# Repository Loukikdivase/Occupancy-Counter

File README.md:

# Occupancy Counter

by: Loukik-Sachin Divase, Rudy Marvyn Kalisetty-Appadu

**Faculty of Technology and Bionics**

***Rhine-Waal University of Applied Sciences***

Date: 16 January 2025

----

## Abstract

The occupancy counter is designed to ensure a seamless flow of people, especially on a busy day. The system tracks the number of people entering and exiting a room and can be used for libraries, offices, toilets, labs, and more. It features real-time monitoring, status indication using LEDs, compliance with safety regulations, and energy-efficient operation. A microcontroller with IR sensors detects directional movement, updates the LCD display accordingly.

## Table of Contents

- [Abstract](#abstract)
- [1 Introduction](#1-introduction)
- [2 Theory](#2-theory)
- [3 Methodology](#3-methodology)
  - [3.1 Hardware](#31-hardware)
  - [3.2 Software](#32-software)
- [4 Bill of Materials (BOM)](#4-bill-of-materials-bom)
- [5 Results](#5-results)
  - [5 Prototype](#50-prototype)
  - [5.1 Schematic](#51-schematic)
  - [5.2 Board](#52-board)
  - [5.3 UV Masking](#53-uv-masking)
  - [5.4 Etching](#54-etching)
  - [5.5 Drilling](#55-drilling)
  - [5.6 Baking](#56-baking)
  - [5.7 Testing](#57-testing)
  - [5.8 Outsourcing](#58-outsourcing)
- [6 Discussion](#6-discussion)
- [7 Conclusion](#7-conclusion)
- [8 Power Consumption](#8-power-consumption)
- [9 References](#9-references)

## 1 Introduction

Managing space efficiently in crowded environments can be challenging. The people counter helps address this issue by providing real-time tracking of room occupancy.

## 2	Theory

The occupancy counter relies on IR sensors to detect movement direction. The system uses logic to determine whether a person enters or exits, ensuring accurate count tracking. If a person passes through sensor 1(placed outside the room near the door) and sensor 2(placed inside the room near the door), the sensor will count. The sensor will increase the count by 1 if a person passes sensor 1 before sensor 2. The sensor will decrease the count by 1 if the person passes sensor 2 before sensor 1.

## 3	Methodology

### 3.1 Hardware

The system consists of:  
•	Microcontroller (ATmega328p)   
•	16MHz Crystal Oscillator  
•	Infrared LED and photodiode  
•	LCD display (16x2)  
•	Buzzer    
•	LED indicators (Red/Green/Yellow)   
•	battery  
•	Voltage regulator (LM7805)   
•	Dual Comparator (LM393)  
•	resistors  
•	capacitors  
•	inductor  
•	switches  

### 3.2 Software

•	Notepad++ for writing the main program  
•	myAVRboard MK2 for flashing the ATmega328p microcontroller  
•	The program tracks occupancy using IR sensor logic and updates the display accordingly.  

#### Code Snippets

//Reset lock for sensor 1 when signal goes HIGH  

if (sensor1_state && sensor1_locked)  
{  
     sensor1_locked = 0; //Reset lock  
}
            
//Reset lock for sensor 2 when signal goes HIGH  

if (sensor2_state && sensor2_locked)  
{  
     sensor2_locked = 0;  // Reset lock  
}  

## 4 BOM

| No. | Qty. | Manufacturer | Component | Ordering Code (Manufacturer) | Vendor | Ordering Code (Vendor) | Price per Unit (€) | Price (€) | Link |
|----|----|--------------|-----------|-------------------------|--------|----------------|----------------|----------|------|
| 1  | 1  | Texas Instruments | 5V Voltage Regulator SMD | LM7805MPX/NOPB | Mouser | 595-LM7805MPX/NOPB | 1.31 | 1.31 | [Link](https://www.mouser.de/ProductDetail/Texas-Instruments/LM7805MPX-NOPB?qs=gO6GG99qvRCSwIVAoVKHPw%3D%3D) |
| 2  | 4  | Atmel | ATmega328P-PU S | - | HSRW | 1712 | 2.51 | 2.51 |  |
| 3  | 4  | - | 16MHz Crystal Oscillator | QD LFXTALO03240 | Reichelt | - | 0.43 | 0.43 | [Link](https://www.reichelt.de/standardquarz-grundton-16-mhz-iqd-lfxtal003240-p245409.html?&trstct=pos_0&nbc=1) |
| 4  | 2  | - | 22pF Capacitor | RND 150MT15N2202 | Reichelt | - | 0.02 | 0.04 | [Link](https://www.reichelt.de/smd-kerko-0402-22-pf-16-v-1-mlec-rnd-150mt15n2202-p225449.html?&trstct=pos_4&nbe=1) |
| 5  | 4  | - | 10k Ohm Resistor | - | HSRW | 621 | 0.01 | 0.04 | [Link](https://ee.hsrw.org/) |
| 6  | 2  | Vishay/BC Components | 220uF Capacitor, 10V DC | MAL214097403E3 | Mouser | 594-MAL214097403E3 | 1.97 | 3.94 | [Link](https://www.mouser.de/ProductDetail/Vishay-BC-Components/MAL214097403E3?qs=aJI9t0tCUIVP9cSclwINCQ%3D%3D) |
| 7  | 5  | - | LEDs | - | HSRW | 471,497,498 | 0.06 | 0.24 | [Link](https://ee.hsrw.org/) |
| 8  | 7  | - | 220 Ohm Resistor | - | HSRW | 579 | 0.01 | 0.07 | [Link](https://ee.hsrw.org/) |
| 9  | 1  | - | LCD Display 16x2 | DEBO LCD16X2 BL | Reichelt | - | 4.65 | 4.65 | [Link](https://www.reichelt.de/entwicklerboards-display-16-x-2-zeichen-blau-debo-led16x2-bl-p335002.html?&trstct=pos_1&nbe=1) |
| 10 | 1  | - | 28-Pin IC Socket | - | HSRW | 630 | 0.21 | 0.21 | [Link](https://ee.hsrw.org/) |
| 11 | 2  | - | Push Button | TASTER 9305 | Reichelt | - | 0.20 | 0.40 | [Link](https://www.reichelt.de/kurzhubtaster-6x6mm-hoehe-8-Omm-12v-vertikal-taster-9305-p44586.html) |
| 12 | 2  | Everlight | Infrared Diode (940nm, emitter) | IR 7373C EVL | Reichelt | - | 0.15 | 0.30 | [Link](https://www.reichelt.de/infrarot-diode-gaalas-940-nm-50-5-mm-t-1-3-4-ir-7373c-evl-p219706.html?&trstct=vrt_pdn&nbe=1) |
| 13 | 6  | - | 0.1µF Capacitor SM | 0.1/63RAD | HSRW | 372 | 0.03 | 0.18 | [Link](https://ee.hsrw.org/) |
| 14 | 2  | Vishay | Phototransistor (Receiver) | BPV10NF | Reichelt | - | 0.35 | 0.70 | [Link](https://www.reichelt.de/pin-fotodiode-5mm-tageslichfilter-20-60-a-870-950nm-bpv-10nf-p146650.html?&trstct=vrt_pdn&nbe=1) |
| 15 | 4  | Aragonesa de Components | Potentiometer (10k Ohm) | ACP 6-S 10K | Reichelt | - | 0.21 | 0.84 | [Link](https://www.reichelt.de/einstellpotentiometer-stehend-10-kohm-6-mm-acp-6-s-10k-p110242.html?&trstct=vrt_pdn&nbe=1) |
| 16 | 1  | STMicroelectronics | LM393 Comparator | LM393 D STM | Reichelt | - | 0.21 | 0.21 | [Link](https://www.reichelt.de/komparator-18v-36v-2-fach-so-8-lm-393-d-stm-p348702.html?&trstct=pos_O&nbe=1) |
| 17 | 1  | - | 2-Pin Angled Connector (Male) | PSS 254/3W | Reichelt | - | 0.06 | 0.06 | [Link](https://www.reichelt.de/printstecker-einzelstecker-gewinkelt-3-polig-pss-254-3w-p14910.html) |
| 18 | 1  | OURNS | 10µH Inductor, 10% Tolerance | CC453232A-100KL | Mouser | 652-CC453232A-100KL | 0.47 | 0.47 | [Link](https://www.mouser.de/ProductDetail/Bourns/CC453232A-100KL?qs=sPbYRqrBIVk4tmhOTVDWBA%3D%3D) |
| 19 | 1  | - | Battery | - | HSRW | - | 1.00 | 1.00 | [Link](https://ee.hsrw.org/) |
| 20 | 1  | - | 3-Pin Switch | - | HSRW | - | 1.35 | 1.35 | [Link](https://ee.hsrw.org/) |
| 21 | 1  | - | Male Headers | - | HSRW | - | 1.00 | 1.00 | [Link](https://ee.hsrw.org/) |
| 22 | 1  | - | Buzzer | - | HSRW | - | 0.50 | 0.50 | [Link](https://ee.hsrw.org/) |
| 23 | 1  | - | NPN Transistor BC547 | - | HSRW | - | 0.36 | 0.36 | [Link](https://ee.hsrw.org/) |

## 5	Results

### Prototype

### 5.1 Schematic

### 5.2 board

### 5.3 UV Masking

### 5.4 Etching

### 5.5 Drilling

### 5.6 Baking

### 5.7 Testing

### 5.8 Outsourcing

## version 2 (additional)

### Schematic

### Board

## 6	Discussion

The system performs well in controlled conditions. However, environmental factors such as lighting variations may affect sensor accuracy. Calibration is necessary for optimal performance.

What exactly happens? 
The person must pass both sensors to register the count since our product is directional.

## 7	Conclusion

As aspiring engineers, we believe that this project was a success. However, there might be some unsolved challenges that we did not encounter, and we would be more than happy to address them in the future. Future work could involve integrating wireless data transmission for monitoring remotely.

## 8	Power Consumption

Total power consumption: 1.29W, where V = 6V and I = 0.22A

Actual useful power consumption: 1W,  where V = 4.85V and I = 0.21A.

## 9	References

* [1] https://shop.myavr.de/Systemboards%20und%20Programmer/myAVR%20Board%20MK2,%20best%C3%BCckt.htm?sp=article.sp.php&artID=40

* [2] https://docs.arduino.cc/hardware/uno-rev3/

* [3] https://github.com/Loukikdivase/Occupancy-Counter/tree/main/resources

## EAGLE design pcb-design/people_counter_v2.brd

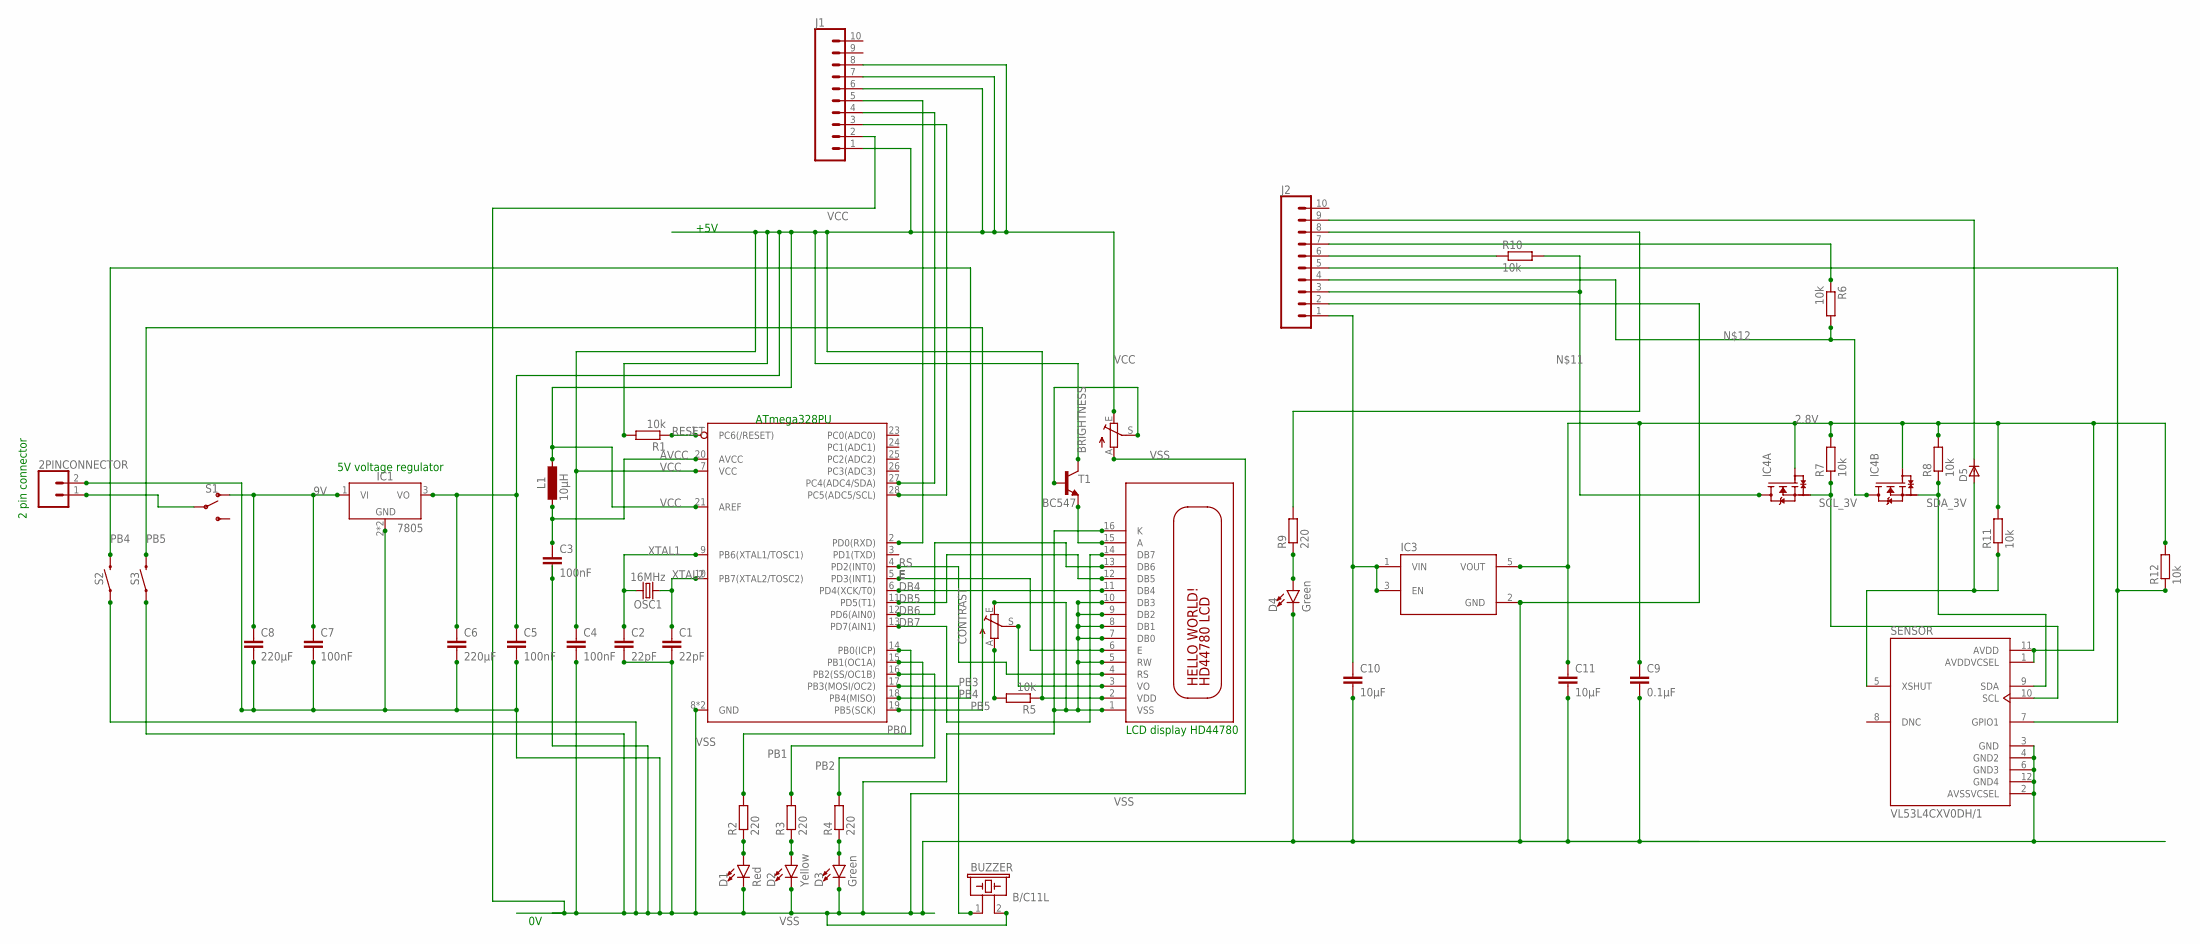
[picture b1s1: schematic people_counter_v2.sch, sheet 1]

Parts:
2PINCONNECTOR: CONN_02; 1X02
BRIGHTNESS: TRIM_EU-PT10S; PT-10S
BUZZER: B/C11L
C1, C2: 22pF; C0805
C3, C4, C5, C7: 100nF; C0805
C6, C8: 220µF; C0805
C9: 0.1µF; C0805
C10, C11: 10µF; C0805
CONTRAST: TRIM_EU-PT10S; PT-10S
D1: Red; LED-0603
D2: Yellow; LED-0603
D3, D4: Green; LED-0603
D5: 1N4148WS; SOD323F
IC1: 7805; SOT230P700X170-4
IC2: 328P; DIP28
IC3: MIC5504-2.8YM5-TR; SOT95P280X145-5N
IC4: DMN63D8LDW-7; SOT363
J1, J2: CONN_10"; 1X10
L1: 10µH; L1812
OSC1: 16MHz; HC49US
R1, R5, R6, R7, R8, R10, R11, R12: 10k; R0603
R2, R3, R4, R9: 220; R0603
S1: SWITCH-SPDT-PTH-11.6X4.0MM; SWITCH_SPDT_PTH_11.6X4.0MM
S2, S3: MOMENTARY-SWITCH-SPST-PTH-6.0MM; TACTILE_SWITCH_PTH_6.0MM
SENSOR: VL53L4CXV0DH/1; XCDR_VL53L4CXV0DH/1
T1: BC547; TO92
X1: HD44780LCD-1602; LCD1602

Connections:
2.8V: C9.1, C11.1, IC3.5 (VOUT), IC4.G1 (G), IC4.G2 (G), R7.2, R8.2, R11.2, R12.2, SENSOR.1 (AVDDVCSEL), SENSOR.11 (AVDD)
9V: C7.1, C8.1, IC1.1 (VI), S1.1 (O)
AVCC: C3.1, IC2.20 (AVCC), L1.2
DB4: IC2.6 (PD4(XCK/T0)), X1.11 (DB4)
DB5: IC2.11 (PD5(T1)), X1.12 (DB5)
DB6: IC2.12 (PD6(AIN0)), X1.13 (DB6)
DB7: IC2.13 (PD7(AIN1)), X1.14 (DB7)
E: IC2.5 (PD3(INT1)), X1.6 (E)
GREEN: D3.A, R4.1
unnamed: J2.6, R10.1
unnamed: D4.A, R9.1
unnamed: D5.C, J2.9
unnamed: 2PINCONNECTOR.1, S1.2
unnamed: IC2.2 (PD0(RXD)), J1.5
unnamed: D5.A, R11.1, SENSOR.5 (XSHUT)
unnamed: CONTRAST.A, R5.2
unnamed: J2.5, R12.1, SENSOR.7 (GPIO1)
unnamed: IC4.D1 (D), J2.3, R10.2
unnamed: IC4.D2 (D), J2.4, R6.2
unnamed: BRIGHTNESS.S, T1.2 (B)
unnamed: J2.8, R9.2
unnamed: J2.7, R6.1
unnamed: C10.1, IC3.1 (VIN), IC3.3 (EN), J2.1
unnamed: T1.1 (E), X1.15 (A)
PB0: IC2.14 (PB0(ICP)), R2.2
PB1: IC2.15 (PB1(OC1A)), R3.2
PB2: IC2.16 (PB2(SS/OC1B)), R4.2
PB3: BUZZER.1, IC2.17 (PB3(MOSI/OC2))
PB4: IC2.18 (PB4(MISO)), S2.3 (2)
PB5: IC2.19 (PB5(SCK)), S3.3 (2)
RED: D1.A, R2.1
RESET: IC2.1 (PC6(/RESET)), R1.1
RS: IC2.4 (PD2(INT0)), X1.4 (RS)
SCL_3V: IC4.S1 (S), R7.1, SENSOR.10 (SCL)
SCL_5V: IC2.28 (PC5(ADC5/SCL)), J1.3
SDA_3V: IC4.S2 (S), R8.1, SENSOR.9 (SDA)
SDA_5V: IC2.27 (PC4(ADC4/SDA)), J1.4
VCC: BRIGHTNESS.E, C4.1, C5.1, C6.1, IC1.3 (VO), IC2.7 (VCC), IC2.21 (AREF), J1.1, J1.6, J1.7, J1.8, L1.1, R1.2, R5.1, T1.3 (C), X1.2 (VDD)
VO: CONTRAST.S, X1.3 (VO)
VSS: 2PINCONNECTOR.2, BRIGHTNESS.A, BUZZER.2, C1.2, C2.2, C3.2, C4.2, C5.2, C6.2, C7.2, C8.2, C9.2, C10.2, C11.2, CONTRAST.E, D1.C, D2.C, D3.C, D4.C, IC1.2 (GND), IC1.4 (GND), IC2.8 (GND), IC2.22 (GND), IC3.2 (GND), J1.2, J2.2, S2.1, S3.1, SENSOR.2 (AVSSVCSEL), SENSOR.3 (GND), SENSOR.4 (GND2), SENSOR.6 (GND3), SENSOR.12 (GND4), X1.1 (VSS), X1.5 (RW), X1.7 (DB0), X1.8 (DB1), X1.9 (DB2), X1.10 (DB3), X1.16 (K)
XTAL1: C2.1, IC2.9 (PB6(XTAL1/TOSC1)), OSC1.2
XTAL2: C1.1, IC2.10 (PB7(XTAL2/TOSC2)), OSC1.1
YELLOW: D2.A, R3.1

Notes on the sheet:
5V voltage regulator
2 pin connector
+5V
ATmega328PU
LCD display HD44780

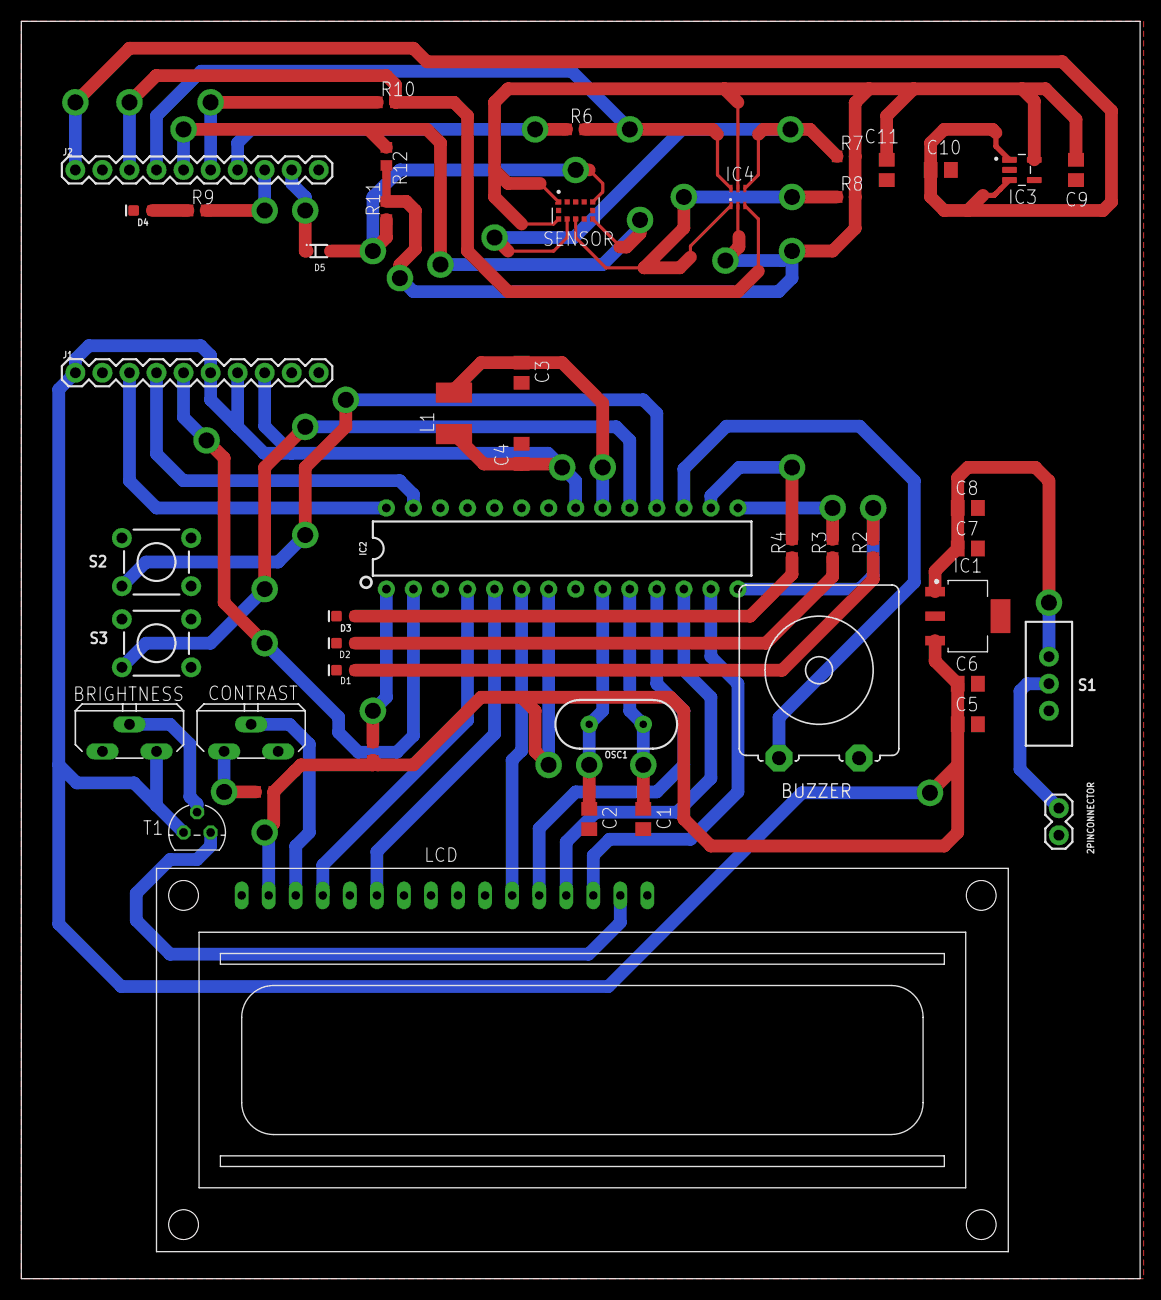
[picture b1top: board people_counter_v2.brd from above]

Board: 2 copper layers, 105.1 x 118.1 mm, 46 parts (0 on the bottom side), 43 nets.

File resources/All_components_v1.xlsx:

Components | Values for resistors (R1 - R11), potentiometers (P1 - P4) in Ohms , capacitors 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 | Remarks | Status
R1 | 10k | Ordered | In use
R2 | 220 | Ordered | In use
R3 | 220 | Ordered | In use
R4 | 220 | Ordered | In use
R5 | 10k | Ordered | In use
R6 | 220 | Ordered | In use
R7 | 220 | Ordered | In use
R8 | 220 | Ordered | In use
R9 | 220 | Ordered | In use
R10 | 10k | Ordered | In use
R11 | 10k | Ordered | In use
C1 | 22p | Ordered | In use
C2 | 22p | Ordered | In use
C3 | 100n | Ordered | In use
C4 | 100n | Ordered | In use
C5 | 100n | Ordered | In use
C6 | 220u | Ordered | In use
C7 | 100n | Ordered | In use
C8 | 220u | Ordered | In use
C9 | 0.1u | Ordered | In use
C10 | 0.1u | Ordered | In use
D1 (IN4001) |  | Ordered | In use
D1 | Red | Ordered | In use
D2 | Yellow | Ordered | In use
D3 | Green | Ordered | In use
D4 | IR (infra red - emitter) - transparent | Ordered | In use
D5 | PT (Photo transistor - receiver) - black | Ordered | In use
D6 | IR (infra red - emitter) - transparent | Ordered | In use
D7 | PT (Photo transistor - receiver) - black | Ordered | In use
D8 | Blue | Ordered | In use
D9 | Blue | Ordered | In use
IC1 | 5V voltage regulator (TS 7805) | Ordered | In use
IC2 | Atmega328P | Ordered | In use
IC3 | LM393 | Ordered | In use
L1 | 10u | Ordered | In use
T1 | NPN transistor | Ordered | In use
S1 | 3 pins switch | Ordered | In use
LCD 16 x 2 (HD44780) |  | Ordered | In use
Potentiometer (for contrast on the LCD screen) | 10k | Ordered | In use
Potentiometer (for brightness on the LCD screen) | 10k | Ordered | In use
Potentiometer (for sensitivity for the IR sensor 1) | 10k | Ordered | In use
Potentiometer (for sensitivity for the IR sensor 2) | 10k | Ordered | In use
Crystal oscillator (Osc1) | 16M | Ordered | In use
2 pins straight connector (for battery) |  | Ordered | In use
Push buttons 1 |  | Ordered | In use
Push buttons 2 |  | Ordered | In use
28-Pin socket for the chip |  | Ordered | In use
USB 2.0 type B mini socket (female) |  | Ordered | not in use
Buzzer |  | Ordered | In use

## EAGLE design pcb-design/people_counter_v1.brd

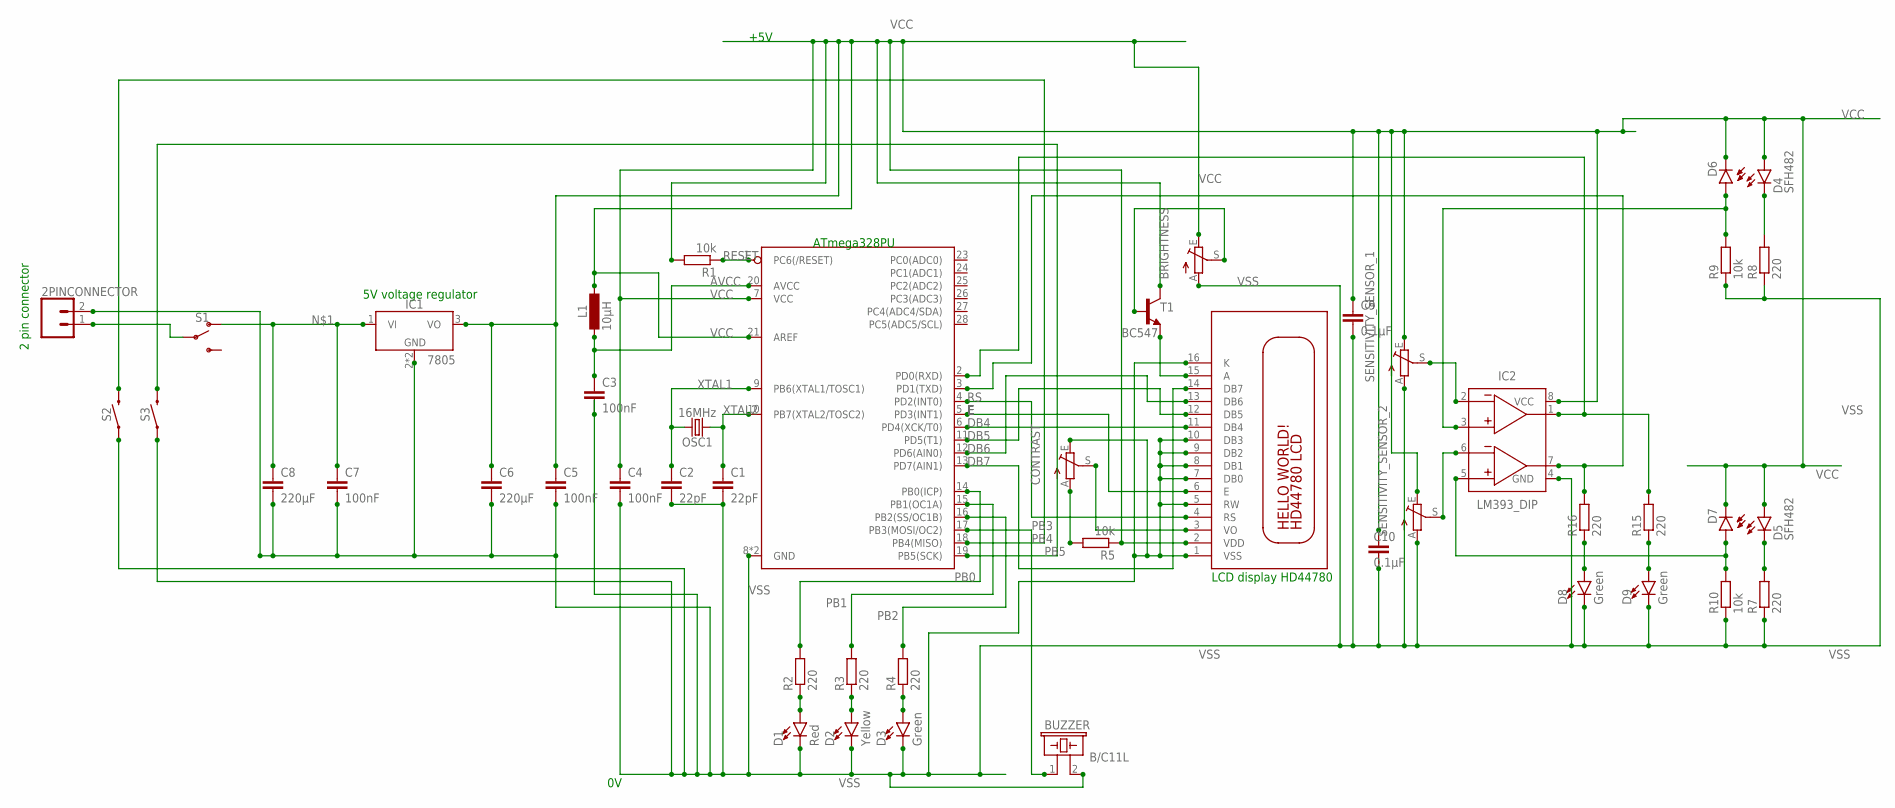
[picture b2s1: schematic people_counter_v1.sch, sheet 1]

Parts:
2PINCONNECTOR: CONN_02; 1X02
BRIGHTNESS: TRIM_EU-PT10S; PT-10S
BUZZER: B/C11L
C1, C2: 22pF; C0805
C3, C4, C5, C7: 100nF; C0805
C6, C8: 220µF; C0805
C9, C10: 0.1µF; C0805
CONTRAST: TRIM_EU-PT10S; PT-10S
D1: Red; LED-0603
D2: Yellow; LED-0603
D3, D8, D9: Green; LED-0603
D4, D5: SFH482
D6, D7: BP104
IC1: 7805; SOT230P700X170-4
IC2: LM393_DIP; DIP826W53P254L959H508Q8B
L1: 10µH; L1812
OSC1: 16MHz; HC49US
R1, R5, R9, R10: 10k; R0603
R2, R3, R4, R7, R8, R15, R16: 220; R0603
S1: SWITCH-SPDT-PTH-11.6X4.0MM; SWITCH_SPDT_PTH_11.6X4.0MM
S2, S3: MOMENTARY-SWITCH-SPST-PTH-6.0MM; TACTILE_SWITCH_PTH_6.0MM
SENSITIVITY_SENSOR_1, SENSITIVITY_SENSOR_2: TRIM_EU-PT10S; PT-10S
T1: BC547; TO92
U1: 328P; DIP28
X1: HD44780LCD-1602; LCD1602

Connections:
AVCC: C3.1, L1.2, U1.20 (AVCC)
DB4: U1.6 (PD4(XCK/T0)), X1.11 (DB4)
DB5: U1.11 (PD5(T1)), X1.12 (DB5)
DB6: U1.12 (PD6(AIN0)), X1.13 (DB6)
DB7: U1.13 (PD7(AIN1)), X1.14 (DB7)
E: U1.5 (PD3(INT1)), X1.6 (E)
unnamed: C7.1, C8.1, IC1.1 (VI), S1.1 (O)
unnamed: BRIGHTNESS.S, T1.2 (B)
unnamed: 2PINCONNECTOR.1, S1.2
unnamed: D1.A, R2.1
unnamed: D2.A, R3.1
unnamed: CONTRAST.A, R5.2
unnamed: D3.A, R4.1
unnamed: D6.A, IC2.3 (+IN1), R9.2
unnamed: D7.A, IC2.5 (+IN2), R10.2
unnamed: D5.K (C), R7.2
unnamed: D4.K (C), R8.2
unnamed: IC2.1 (OUT1), R15.2, U1.2 (PD0(RXD))
unnamed: IC2.7 (OUT2), R16.2, U1.3 (PD1(TXD))
unnamed: IC2.2 (-IN1), SENSITIVITY_SENSOR_1.S
unnamed: IC2.6 (-IN2), SENSITIVITY_SENSOR_2.S
unnamed: T1.1 (E), X1.15 (A)
unnamed: D9.A, R15.1
unnamed: D8.A, R16.1
PB0: R2.2, U1.14 (PB0(ICP))
PB1: R3.2, U1.15 (PB1(OC1A))
PB2: R4.2, U1.16 (PB2(SS/OC1B))
PB3: BUZZER.1, U1.17 (PB3(MOSI/OC2))
PB4: S2.3 (2), U1.18 (PB4(MISO))
PB5: S3.3 (2), U1.19 (PB5(SCK))
RESET: R1.1, U1.1 (PC6(/RESET))
RS: U1.4 (PD2(INT0)), X1.4 (RS)
VCC: BRIGHTNESS.E, C4.1, C5.1, C6.1, C9.1, C10.1, D4.A, D5.A, D6.K (C), D7.K (C), IC1.3 (VO), IC2.8 (VCC), L1.1, R1.2, R5.1, SENSITIVITY_SENSOR_1.E, SENSITIVITY_SENSOR_2.E, T1.3 (C), U1.7 (VCC), U1.21 (AREF), X1.2 (VDD)
VO: CONTRAST.S, X1.3 (VO)
VSS: 2PINCONNECTOR.2, BRIGHTNESS.A, BUZZER.2, C1.2, C2.2, C3.2, C4.2, C5.2, C6.2, C7.2, C8.2, C9.2, C10.2, CONTRAST.E, D1.C, D2.C, D3.C, D8.C, D9.C, IC1.2 (GND), IC1.4 (GND), IC2.4 (GND), R7.1, R8.1, R9.1, R10.1, S2.1, S3.1, SENSITIVITY_SENSOR_1.A, SENSITIVITY_SENSOR_2.A, U1.8 (GND), U1.22 (GND), X1.1 (VSS), X1.5 (RW), X1.7 (DB0), X1.8 (DB1), X1.9 (DB2), X1.10 (DB3), X1.16 (K)
XTAL1: C2.1, OSC1.2, U1.9 (PB6(XTAL1/TOSC1))
XTAL2: C1.1, OSC1.1, U1.10 (PB7(XTAL2/TOSC2))

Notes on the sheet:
5V voltage regulator
2 pin connector
+5V
ATmega328PU
LCD display HD44780

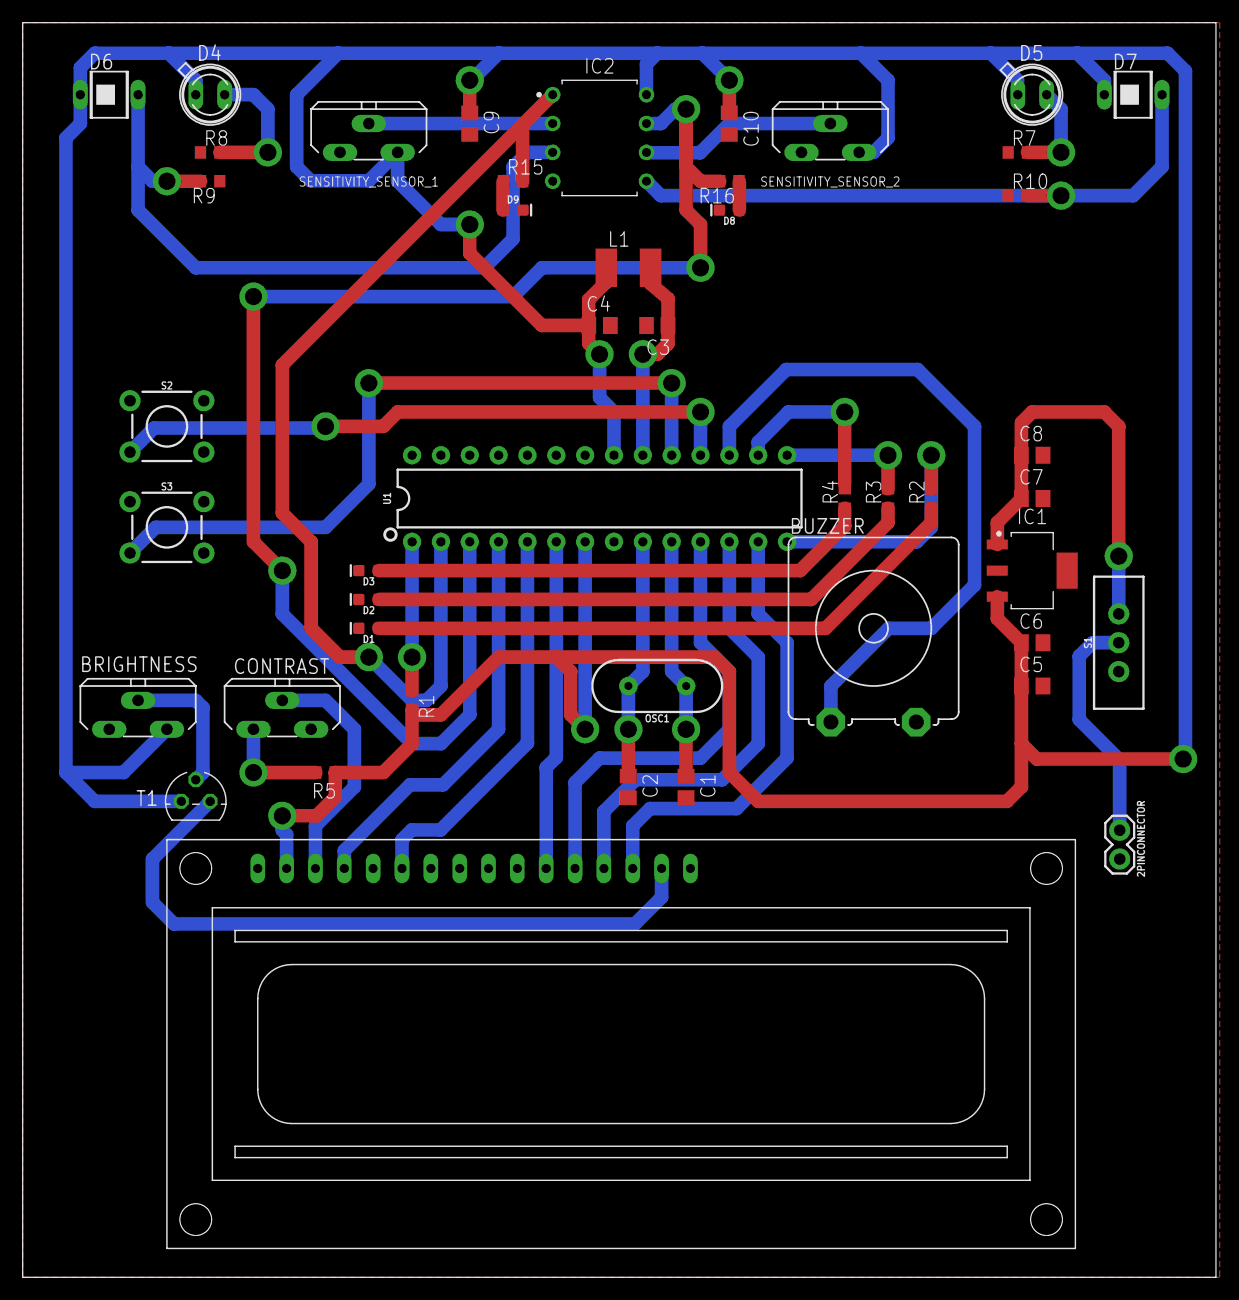
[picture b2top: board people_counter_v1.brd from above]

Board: 2 copper layers, 105.1 x 110.5 mm, 46 parts (0 on the bottom side), 37 nets.

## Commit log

2025-01-16 Create project-idea
2025-01-16 Create presentation
2025-01-16 Create hhh

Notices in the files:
parts and their libraries:
SparkFun-Connectors: Licensing: Creative Commons ShareAlike 4.0 International - https://creativecommons.org/licenses/by-sa/4.0
